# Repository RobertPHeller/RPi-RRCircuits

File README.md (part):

# RPi-RRCircuits

This is a collection of Model Railroad open hardware and open source projects,
using LCC, OpenMRN, and OpenMRN-lite, for the following MCUs and SBCs:

Raspberry Pi, generally as HATs for the "B" flavors (RPi2B, RPi3B and RPi4B).
  (Directories with "HAT" at the end are for these boards.)

Beagle boards, including capes for BeagleBone Black and baseboards for
  PocketBeagles.
  (Directories with "CAPE" at the end are for BeagleBone Blacks,
   directories starting with "BBB" are also boards for the BeagleBone Black,
   directories starting with "PB" or "PocketBeagle" are for the PocketBeagles -
   these boards assume male header pins soldered to the bottom of the 
   PocketBeagle that insert into female header sockets on the base board.)

ESP32 (mostly meant for the Lilygo TTGO-T1 board)
  (Directories starting with "ESP32" are for this board.)

There are a few projects for other boards, including MetroMini (an Adafruit 
mini board that is a Arduino UNO clone), Tiva, and STM's Nucleo board.  The 
directory names will include the name of the board.

Directories ending in OpenMRN contain the Raspberry Pi and Beagle board
software for the various boards.  

These projects were created using Kicad 2013.06.11
(https://launchpad.net/kicad) under CentOS 6 and Kicad 4.0.7 under Ubuntu
18.04. Each subdirectory is one project, and contains a schematic and PCB
design or contains a program for one (or more) projects. There is also
software for the boards using OpenMRN (C++ library for OpenLCB/LCC) for these
projects.

There is a README in each project dir.

## Availble Projects:

1. [16DriverOutputCape](https://github.com/RobertPHeller/RPi-RRCircuits/tree/master/16DriverOutputCape)

    > This is a MCP23017 with two octal buffers meant to drive 16 LEDs (such as 
    > signal lamps). No PWM or special effects.  This board is a Cape for a 
    > BeagleBone Black or Green.  Has address jumpers for the MCP23017 and can be 
    > stacked -- up to 8 of these capes for up to 128 LEDS -- each board has power 
    > terminals for the LEDs.

1. [16DriverOutputHAT](https://github.com/RobertPHeller/RPi-RRCircuits/tree/master/16DriverOutputHAT)

    > This is a MCP23017 with two octal buffers meant to drive 16 LEDs (such as 
    > signal lamps). No PWM or special effects.  This board is a HAT for a 
    > Raspberry Pi 2, 3, or 4.  Has address jumpers for the MCP23017 and can be 
    > stacked -- up to 8 of these hats for up to 128 LEDS -- each board has power 
    > terminals for the LEDs.

1. [16DriverOutputOpenMRN](https://github.com/RobertPHeller/RPi-RRCircuits/tree/master/16DriverOutputOpenMRN)

    > The is the OpenMRN (OpenLCB/LCC) program code for the 16DriverOutput HAT or 
    > Cape boards. Can be build on either a BeagleBoard or a Raspberry Pi for 
    > either. 

1. [16LEDDriver23017SMD](https://github.com/RobertPHeller/RPi-RRCircuits/tree/master/16LEDDriver23017SMD)

    > This is a SMD variant of 16DriverOutputHAT.

1. [16PWMLedDriverCape](https://github.com/RobertPHeller/RPi-RRCircuits/tree/master/16PWMLedDriverCape)

    > This is a PCA9685 with two octal buffers meant to drive 16 LEDs (such as 
    > signal lamps).  This board is much like 16DriverOutputHat, but uses a PWM chip 
    > to allow for special effects and allows for brightness adjustment.  Has 
    > address jumpers for the PCA9685 and can be stacked -- up to 64 boards (WOW) 
    > for up to 1024 LEDs (WOW) -- each board has power terminals for the LEDs.

1. [16PWMLedDriverHat](https://github.com/RobertPHeller/RPi-RRCircuits/tree/master/16PWMLedDriverHat)

    > This is a PCA9685 with two octal buffers meant to drive 16 LEDs (such as 
    > signal lamps).  This board is much like 16DriverOutputHat, but uses a PWM chip 
    > to allow for special effects and allows for brightness adjustment.  Has 
    > address jumpers for the PCA9685 and can be stacked -- up to 64 boards (WOW) 
    > for up to 1024 LEDs (WOW) -- each board has power terminals for the LEDs.

1. [16PWMLedDriverOpenMRN](https://github.com/RobertPHeller/RPi-RRCircuits/tree/master/16PWMLedDriverOpenMRN)

    > This is the OpenMRN (OpenLCB/LCC) program for the 16PWMLedDriver* boards (RPi
    > Hat, BBB Cape, and PocketBeagle board). Can be build on either a BeagleBoard 
    > or a Raspberry Pi for either.

1. [16PWMLedDriverPocketBeagle](https://github.com/RobertPHeller/RPi-RRCircuits/tree/master/16PWMLedDriverPocketBeagle)

    > This is a PCA9685 with two octal buffers meant to drive 16 LEDs (such as
    > signal lamps). This board is much like 16DriverOutputCape, but uses a PWM chip
    > to allow for special effects and allows for brightness adjustment. Has address
    > jumpers for the PCA9685, includes a CAN transceiver with LCC network
    > connectors (RJ45s), 5V power supply for the PocketBeagle, and uses LCC power
    > for the LEDS. It uses female headers for the PocketBeagle (presumes male pin
    > headers soldered to the underside of the PocketBeagle).

1. [BBBCommandStation](https://github.com/RobertPHeller/RPi-RRCircuits/tree/master/BBBCommandStation)

    > Early BeagleBone Black LCC/DCC Command Station board set -- two boards, a cape 
    > and a power board.  Does not include RailComm support.

1. [BBBCommandStationOpenMRN](https://github.com/RobertPHeller/RPi-RRCircuits/tree/master/BBBCommandStationOpenMRN)

    > This is the program for the Beagle Board LCC/DCC/Railcom command 
    > station.  It uses OpenMRN to interface with tha LCC/OpenLCB network
    > to implement a LCC/OpenLCB aware command station node that can 
    > operate DCC/Railcom locomotives.  It should work with any of the
    > Beagle Board addon boards I have designed.  It uses the AM335X's
    > PRUs to generate the DCC signals.  It ises the OpenMRN Console
    > class to communicate over a Tcp/Ip channel with a Tcl/Tk coded
    > GUI program to provide a user friendly point-and-click high level
    > user interface.  

1. [BBBHalfSiding](https://github.com/RobertPHeller/RPi-RRCircuits/tree/master/BBBHalfSiding)

    > Early HalfSiding cape for the Beagle Bone Black. A somewhat all-in-one board
    > for the Beagle Bone Black to manage one half of a siding. This something of a
    > "kitchen sink" board and proably awkard in practice. Probably better off
    > stacking several separate special purpose capes.  I mostly did this as a 
    > "thought experiment" to see what this would look like.  Oh, if it used SMD 
    > parts it might be more compact and might be practical as a single board.

1. [ButtonHat](https://github.com/RobertPHeller/RPi-RRCircuits/tree/master/ButtonHat)

    > This is a RPi HAT board to interface up to 12 push buttons with hardware 
    > debouncing (using 74ahc14 Hex Schmitt-Trigger Inverters) to a RPi.  Jumpers 
    > are used to map the buttons to GPIO pins.  This was a simple "thought 
    > experiment" to see if this was possible.

1. [CANHat](https://github.com/RobertPHeller/RPi-RRCircuits/tree/master/CANHat)

    > This is the original CAN Hat, using the MCP2515 CAN IF Chip and a MCP2551 
    > transceiver chip.

1. [CANHat2](https://github.com/RobertPHeller/RPi-RRCircuits/tree/master/CANHat2)

    > This is the second incarnation of the CAN Hat, also using the MCP2515 and 
    > MCP2551 chips.

1. [CANHat3](https://github.com/RobertPHeller/RPi-RRCircuits/tree/master/CANHat3)

    > This is the third incarnation of the CAN Hat, also using the MCP2515 and 
    > MCP2551 chips.

1. [DCCOD_SMD](https://github.com/RobertPHeller/RPi-RRCircuits/tree/master/DCCOD_SMD)

    > Single current sensing occupancy detector, meant for ESP32-16xDCCOD or 
    > simular.  Meant as a thought experiment to see what this would cost, etc.

1. [DCCShield](https://github.com/RobertPHeller/RPi-RRCircuits/tree/master/DCCShield)

    > Simple DCC driver shield for Arduino.

1. [DCCTiva](https://github.com/RobertPHeller/RPi-RRCircuits/tree/master/DCCTiva)

    > Simple DCC Driver board for Tiva.

1. [DualUncouplerHAT](https://github.com/RobertPHeller/RPi-RRCircuits/tree/master/DualUncouplerHAT)

    > This a dual driver for a electromagnetic uncoupler coil.  It features a 
    > pair of 555 type timers (in the form of a 556 dual timer) driving a TIP120 
    > power darlington.  It uses GPIO pins 21 and 22 (BCM 5 and 6, physical pins 
    > 29 and 31).

1. [DualUncouplerHAT1](https://github.com/RobertPHeller/RPi-RRCircuits/tree/master/DualUncouplerHAT1)

    > This is the same as DualUncouplerHAT, except it uses GPIO pins 23 and 24 
    > (BCM 13 and 19, physical pins 33 and 35).

1. [ESP32-16LedDriver](https://github.com/RobertPHeller/RPi-RRCircuits/tree/master/ESP32-16LedDriver)

    > 16 on/off LED Driver board using a MCP23017.

1. [ESP32-16PWMLedDriver](https://github.com/RobertPHeller/RPi-RRCircuits/tree/master/ESP32-16PWMLedDriver)

    > 16 LED PWM driver board using a PCA9685.

1. [ESP32-16xDCCOD](https://github.com/RobertPHeller/RPi-RRCircuits/tree/master/ESP32-16xDCCOD)

    > Backplane for up to 16 DCCOD_SMD's using a ESP32 MCU.  Meant as a thought 
    > experiment to see what this would cost, etc.

1. [ESP32-C3-Booster](https://github.com/RobertPHeller/RPi-RRCircuits/tree/master/ESP32-C3-Booster)

    > ESP32 C3 based DCC Booster.

1. [ESP32-C3-BoosterOpenMRNIDF](https://github.com/RobertPHeller/RPi-RRCircuits/tree/master/ESP32-C3-BoosterOpenMRNIDF)

    > 

1. [ESP32-D0WD-V3-MultiFunctionOpenMRNIDF](https://github.com/RobertPHeller/RPi-RRCircuits/tree/master/ESP32-D0WD-V3-MultiFunctionOpenMRNIDF)

    > 

1. [ESP32-HalfSiding](https://github.com/RobertPHeller/RPi-RRCircuits/tree/master/ESP32-HalfSiding)

    > First draft of a ESP32 HalfSiding node using a MCP23017 on/off signal lamps.

1. [ESP32-MultiFunction](https://github.com/RobertPHeller/RPi-RRCircuits/tree/master/ESP32-MultiFunction)

    > This is a circuit board that supports an ESP32 Dev Kit board or TTGO-T1 board
    > to manage a range of possible interlocking plants or other model railroad
    > situations. It contains four stall motor drivers with point sense, four CT
    > Coil type occupancy detectors, four Schmitt-Trigger inputs (for push buttons),
    > four driver outputs, and 16 PWM LED drivers.

1. [ESP32-PWMHalfSiding](https://github.com/RobertPHeller/RPi-RRCircuits/tree/master/ESP32-PWMHalfSiding)

    > This is a circuit board that supports an ESP32 Dev Kit board or TTGO-T1 board 
    > to manage one half (one end) of a siding.  This board can also be used to 
    > manage two bi-directional single track ABS blocks or one bi-directional dual 
    > track ABS block.  There are other trackwork cases this board can handle as 
    > well.  

1. [ESP32-PWMHalfSidingSMD-T7](https://github.com/RobertPHeller/RPi-RRCircuits/tree/master/ESP32-PWMHalfSidingSMD-T7)

    > This is a circuit board that supports an ESP32 Dev Kit board or TTGO-T1 board 
    > to manage one half (one end) of a siding.  This board can also be used to 
    > manage two bi-directional single track ABS blocks or one bi-directional dual 
    > track ABS block.  There are other trackwork cases this board can handle as 
    > well.  

1. [ESP32-PWMHalfSidingSMD](https://github.com/RobertPHeller/RPi-RRCircuits/tree/master/ESP32-PWMHalfSidingSMD)

    > This is a circuit board that supports an ESP32 Dev Kit board or TTGO-T1 board 
    > to manage one half (one end) of a siding.  This board can also be used to 
    > manage two bi-directional single track ABS blocks or one bi-directional dual 
    > track ABS block.  There are other trackwork cases this board can handle as 
    > well.  

1. [ESP32-S3-MultiFunction](https://github.com/RobertPHeller/RPi-RRCircuits/tree/master/ESP32-S3-MultiFunction)

    > This is a LCC node circuit board that is based around an Espressif ESP32-S3FN8
    > MCU to manage and operate a collection of model railroad sensors and
    > actuators. 

1. [ESP32-S3-MultiFunctionOpenMRNIDF](https://github.com/RobertPHeller/RPi-RRCircuits/tree/master/ESP32-S3-MultiFunctionOpenMRNIDF)

    > 

1. [ESP32_mini_KiCad_Library](https://github.com/RobertPHeller/RPi-RRCircuits/tree/master/ESP32_mini_KiCad_Library)

    > KiCad symbol and footprint for the ESP32 Mini, the ESP32 clone of the Wemos D1 mini with more pins and more power!
    > There is some info on the boards [here](https://www.reddit.com/r/esp8266/comments/a93raj/wemos_ttgo_mini_d1_esp32/). It seems to be a Wemos clone, but is def. not made by them. I really like the boards for the small size and cheap price while giving me the power of an ESP32 and much more IO compared to the Wemos D1 mini.

1. [ESP32ABSBoard](https://github.com/RobertPHeller/RPi-RRCircuits/tree/master/ESP32ABSBoard)

    > ESP32 ABS (Automatic Block Signal) board.  Very simple board: one block 
    > detector, 8 LED drivers.

1. [ESP32BaseBoard](https://github.com/RobertPHeller/RPi-RRCircuits/tree/master/ESP32BaseBoard)

    > ESP32 Base board.  Base starting point for a ESP32 node.

1. [ESP32MRNSketches](https://github.com/RobertPHeller/RPi-RRCircuits/tree/master/ESP32MRNSketches)

    > ESP32 Arduino / OpenMRNLite sketches for the ESP32 boards.

1. [ESP32QuadOCDect](https://github.com/RobertPHeller/RPi-RRCircuits/tree/master/ESP32QuadOCDect)

    > ESP32 Quad Occupancy Detector node.

1. [ESP32QuadSMCSense](https://github.com/RobertPHeller/RPi-RRCircuits/tree/master/ESP32QuadSMCSense)

    > ESP32 Quad Stall Motor w/ sense node.

1. [LCCCANCape](https://github.com/RobertPHeller/RPi-RRCircuits/tree/master/LCCCANCape)

    > LCC/CAN Transceiver Cape for the Beagle Bone.

1. [LEDDriverHat](https://github.com/RobertPHeller/RPi-RRCircuits/tree/master/LEDDriverHat)

    > Eight LED drivers.  Jumpers to select GPIO pins.

1. [MCP23017Hat](https://github.com/RobertPHeller/RPi-RRCircuits/tree/master/MCP23017Hat)

    > This is a 16 pin I2C port expander using a MCP230017.

1. [OpenMRNIDF](https://github.com/RobertPHeller/RPi-RRCircuits/tree/master/OpenMRNIDF)

    > This is an exported version of the OpenMRN library for the ESP32 which is
    > usable as an ESP-IDF component.

1. [PBCommandStation](https://github.com/RobertPHeller/RPi-RRCircuits/tree/master/PBCommandStation)

    > Original through hole version of the Pocket Beagle LCC/DCC Command Station.
    > This design is depreciated -- see PocketBeagleCommandStation and 
    > PocketBeagleCommandStation_SMD for a current design.

1. [PocketBeagleCommandStation](https://github.com/RobertPHeller/RPi-RRCircuits/tree/master/PocketBeagleCommandStation)

    > Through hole version of the PocketBeagle LCC/DCC Command Station. This is a
    > DCC command station that is a LCC node. It implements the OpenLCB train
    > protocol node over LCC and converts that to DCC commands. It includes a
    > booster and puts the DCC signal on the LCC bus (pins 4 and 5). It implements a
    > programming track and implements Railcom. The Command Station uses a
    > PocketBeagle as the processing element and uses the PRUs (Programmable
    > Realtime Units) to generate the DCC signal. (See
    > [PocketBeagleCommandStation_SMD](https://github.com/RobertPHeller/RPi-RRCircuits/tree/master/PocketBeagleCommandStation_SMD)
    > for a SMD version.)

1. [PocketBeagleCommandStation_SMD](https://github.com/RobertPHeller/RPi-RRCircuits/tree/master/PocketBeagleCommandStation_SMD)

    > SMD version of the PocketBeagle LCC/DCC Command Station.  This is a
    > DCC command station that is a LCC node. It implements the OpenLCB train
    > protocol node over LCC and converts that to DCC commands. It includes a
    > booster and puts the DCC signal on the LCC bus (pins 4 and 5). It implements a
    > programming track and implements Railcom. The Command Station uses a
    > PocketBeagle as the processing element and uses the PRUs (Programmable
    > Realtime Units) to generate the DCC signal. (See
    > [PocketBeagleCommandStation](https://github.com/RobertPHeller/RPi-RRCircuits/tree/master/PocketBeagleCommandStation)
    > for a through hole version.)

1. [PocketBeagleMultifuntion](https://github.com/RobertPHeller/RPi-RRCircuits/tree/master/PocketBeagleMultifuntion)

    > This is a circuit board that supports a PocketBeagle board to manage a range
    > of possible interlocking plants or other model railroad situations. It
    > contains four stall motor drivers with point sense, four CT Coil type
    > occupancy detectors, four Schmitt-Trigger inputs (for push buttons), four
    > driver outputs, 8 GPIO pins in a 5x2 header, and 16 PWM LED drivers. 

1. [PocketBeagleMultifuntionOpenMRN](https://github.com/RobertPHeller/RPi-RRCircuits/tree/master/PocketBeagleMultifuntionOpenMRN)

    > OpenMRN program for the PocketBeagleMultifuntion board.

1. [PocketBeagleQuadOCDect](https://github.com/RobertPHeller/RPi-RRCircuits/tree/master/PocketBeagleQuadOCDect)

    > PocketBeagle Quad Occupancy Detector.

1. [PocketBeagleQuadSMCSense](https://github.com/RobertPHeller/RPi-RRCircuits/tree/master/PocketBeagleQuadSMCSense)

    > PocketBeagle Quad Stall Motor w/ Sense.

1. [QuadOCDectCape](https://github.com/RobertPHeller/RPi-RRCircuits/tree/master/QuadOCDectCape)

    > Quad Occupancy detector Cape (for a Beagle Bone).

1. [QuadOCDectHat](https://github.com/RobertPHeller/RPi-RRCircuits/tree/master/QuadOCDectHat)

    > Quad Occupancy detector Hat for Raspberry Pi.

1. [QuadOCDectOpenMRN](https://github.com/RobertPHeller/RPi-RRCircuits/tree/master/QuadOCDectOpenMRN)

    > OpenMRN (LCC / OpenLCB) program for Quad Occupancy Detector boards for Linux
    > SBCs.

1. [QuadSMC](https://github.com/RobertPHeller/RPi-RRCircuits/tree/master/QuadSMC)

    > This is a generic quad verison of SMCSenseHAT.

1. [QuadSMCSenseCape](https://github.com/RobertPHeller/RPi-RRCircuits/tree/master/QuadSMCSenseCape)

    > Quad Stall Motor w/ Sense Cape for a Beagle Bone.

1. [QuadSMCSenseHat](https://github.com/RobertPHeller/RPi-RRCircuits/tree/master/QuadSMCSenseHat)

    > Quad Stall Motor w/ Sense Hat for a Raspberry Pi.

1. [QuadSMCSenseOpenMRN](https://github.com/RobertPHeller/RPi-RRCircuits/tree/master/QuadSMCSenseOpenMRN)

    > OpenMRN (LCC / OpenLCB) program for Linux SBC with QuadSMCSense addon boards.

1. [QuadUncoupler](https://github.com/RobertPHeller/RPi-RRCircuits/tree/master/QuadUncoupler)

    > This is a generic qad version of DualUncouplerHAT.

1. [SignalHAT](https://github.com/RobertPHeller/RPi-RRCircuits/tree/master/SignalHAT)

    > This is a hat containing a MAX7221 driven off level shifted SPI.  It can 
    > drive up to 8 common-cathode signals of up to 8 LEDs each.

1. [SMCSenseHAT](https://github.com/RobertPHeller/RPi-RRCircuits/tree/master/SMCSenseHAT)

    > This is a dual stall motor driver and point sense circuit.  The stall 
    > motor driver uses a MPQ3725A transistor to allow driving either multiple 
    > Tortoises in parallel (eg for a crossover) or newer Switchmaster or 
    > Torquemaster which draw more current than the LM324 can handle.  Also 
    > included is a point sense circuit built from a RS Flip Flop made from 
    > 2-input NAND gates.  The point sense circuit expects to be connected to a 
    > single pole double throw switch, either a built in one in the Tortoise or 
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
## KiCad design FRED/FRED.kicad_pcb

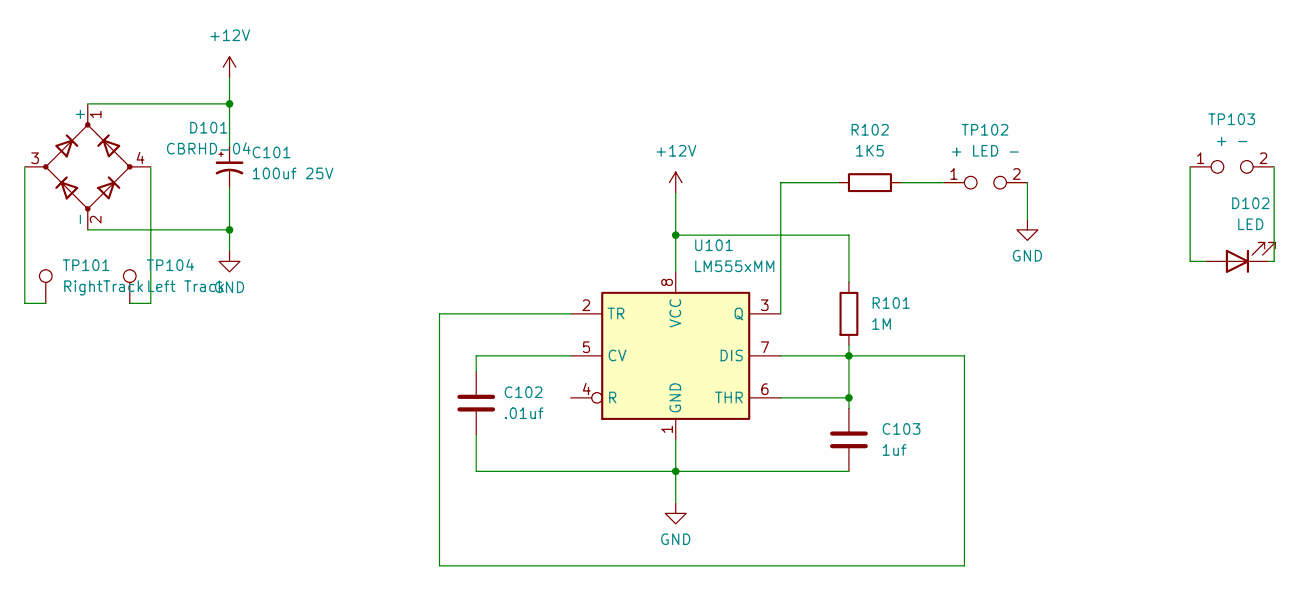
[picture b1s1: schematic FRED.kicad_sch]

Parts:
C101: 100uf 25V; CP_EIA-7361-438_AVX-U; Mouser Part Number 581-TRJU107K025RRJV
C102: .01uf; C_0402_1005Metric; Mouser Part Number 603-CC402JRX7R8BB103
C103: 1uf; C_0402_1005Metric; Mouser Part Number 603-CC402KRX5R6BB105
D101: CBRHD-04; SOP250P700X290-4N; Mouser Part Number 610-CBRHD04-PB
D102: LED; LED_0201_0603Metric; Mouser Part Number 743-IN-S21AT5R
R101: 1M; R_0402_1005Metric; Mouser Part Number 652-CR0402FX-1003GLF
R102: 1K5; R_0402_1005Metric; Mouser Part Number 652-CR0402FX-1501GLF
TP101: RightTrack; Track Pickup Pad
TP102: + LED -; SolderWire-0.1sqmm_1x02_P3.6mm_D0.4mm_OD1mm
TP103: + -; SolderPads_1x2_1.2mm
TP104: Left Track; Track Pickup Pad
U101: LM555xMM; VSSOP-8_3.0x3.0mm_P0.65mm; Mouser Part Number 926-LM555CMMX/NOPB

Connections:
+12V: C101.1, D101.1 (+), R101.1, U101.8 (VCC)
GND: C101.2, C102.2, C103.2, D101.2 (-), TP102.2, U101.1 (GND)
unnamed: C102.1, U101.5 (CV)
unnamed: C103.1, R101.2, U101.2 (TR), U101.6 (THR), U101.7 (DIS)
unnamed: D101.3, TP101.1
unnamed: D101.4, TP104.1
unnamed: D102.1 (K), TP103.2
unnamed: D102.2 (A), TP103.1
unnamed: R102.1, U101.3 (Q)
unnamed: R102.2, TP102.1

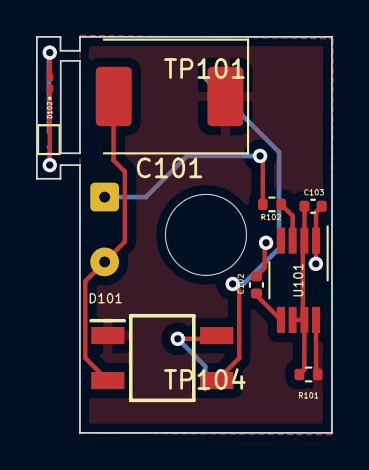
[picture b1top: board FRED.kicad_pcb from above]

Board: 2 copper layers, 16.4 x 22.0 mm, 12 parts (0 on the bottom side), 10 nets.

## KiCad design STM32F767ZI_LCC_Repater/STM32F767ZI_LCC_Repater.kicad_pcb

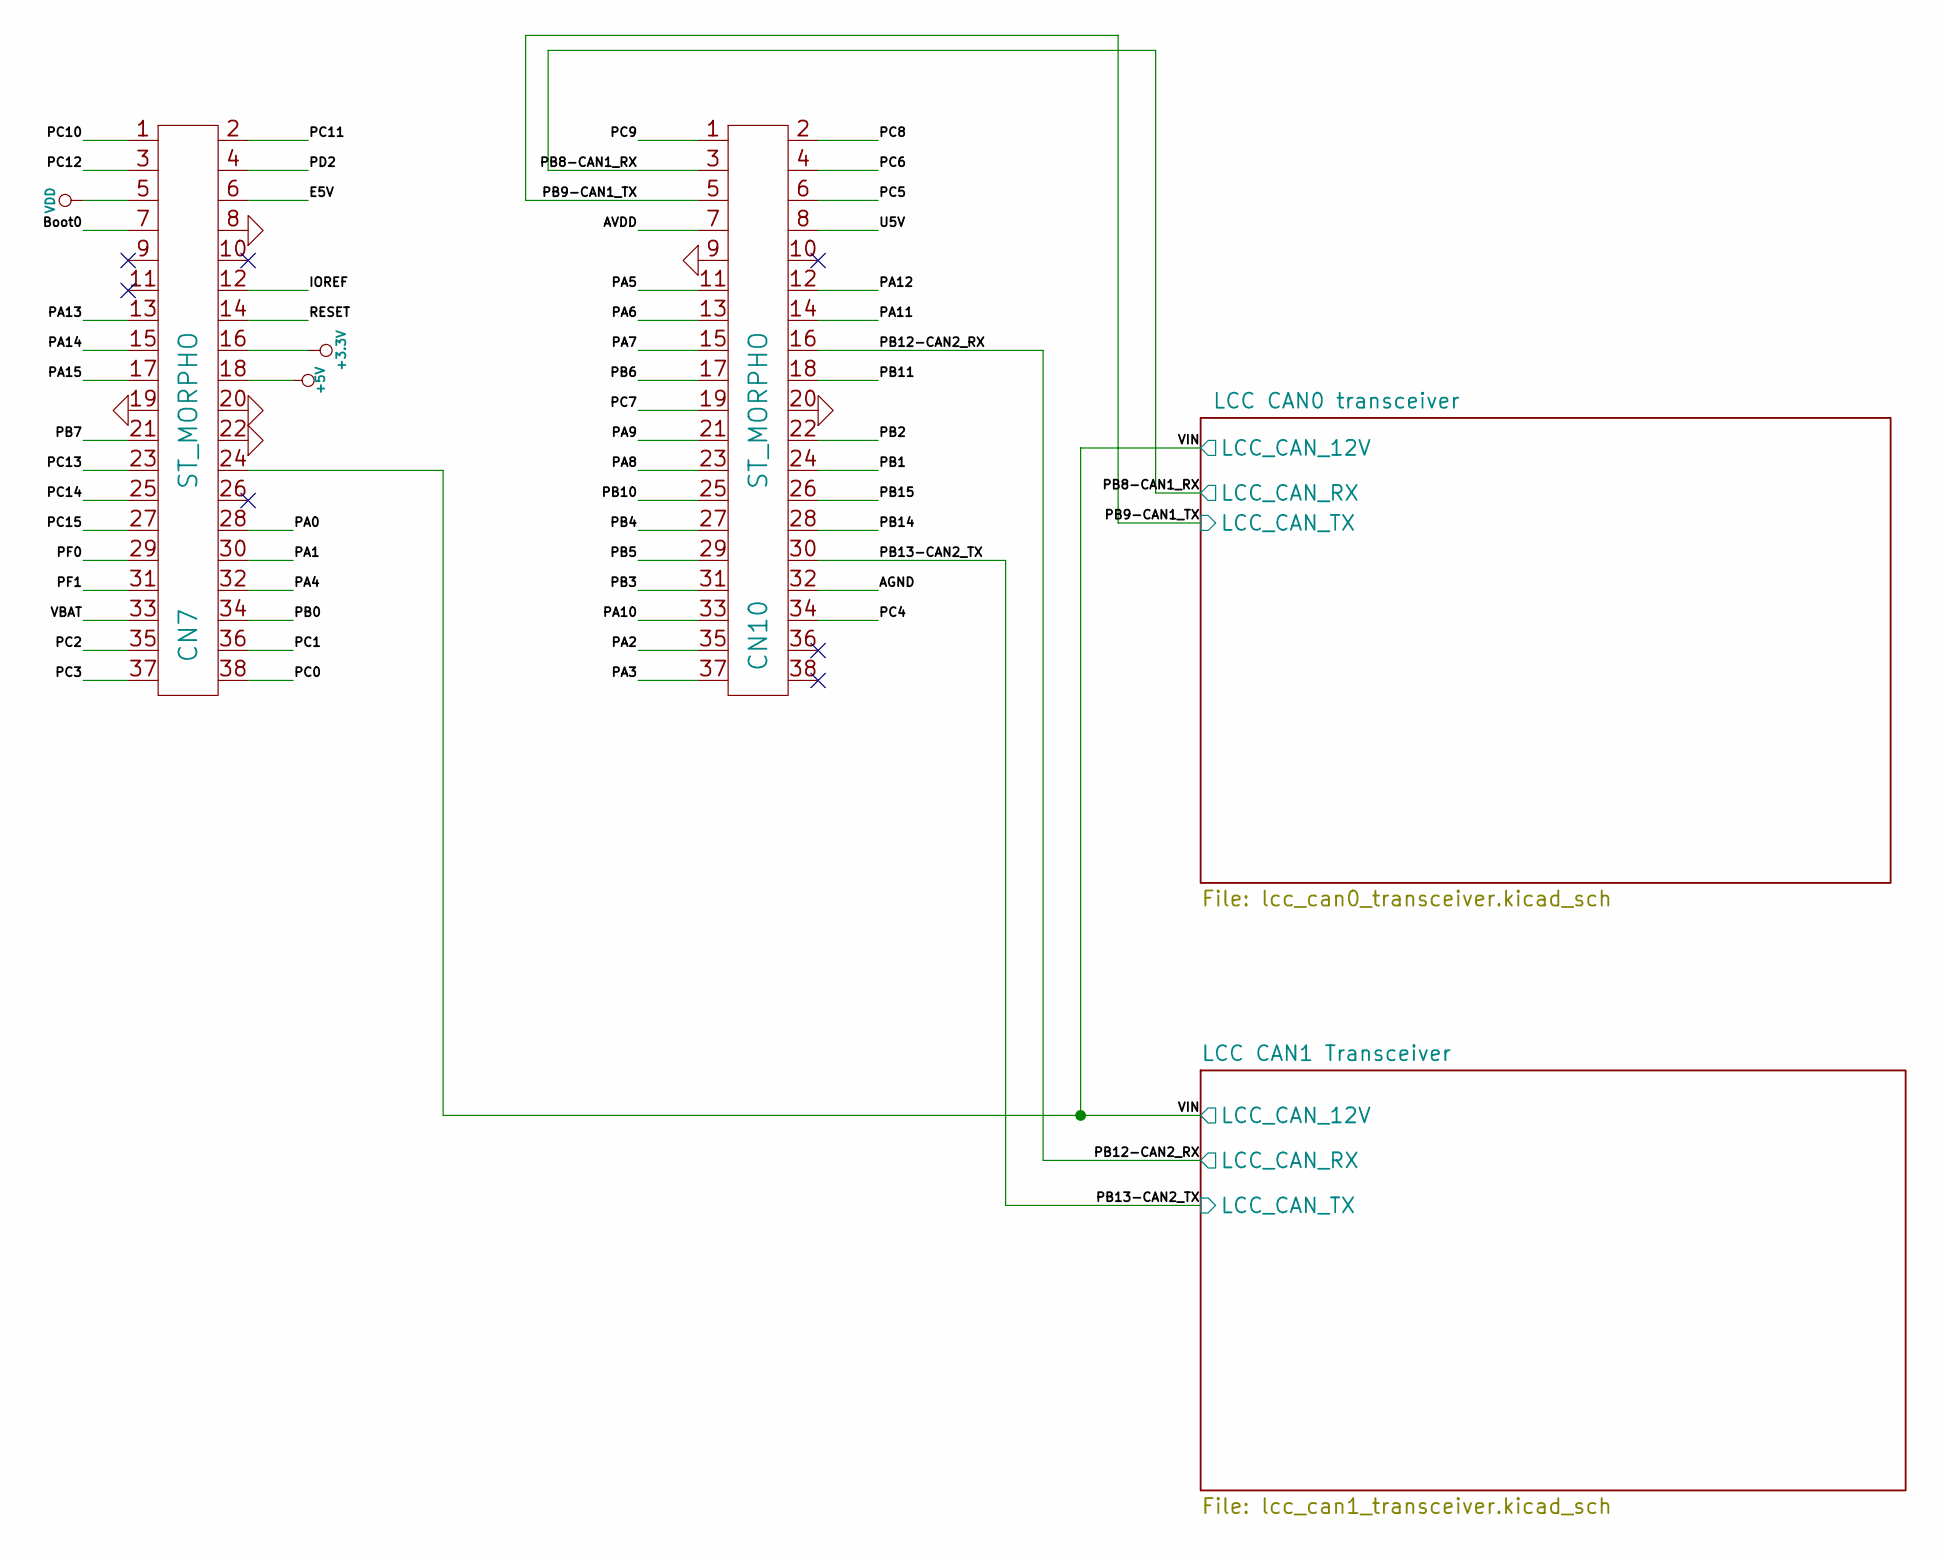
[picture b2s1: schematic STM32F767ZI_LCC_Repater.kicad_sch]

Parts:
CN7, CN10: ST_MORPHO; ST_Morpho

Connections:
+3.3V: CN7.16; also elsewhere on the board
+5V: CN7.18
/AGND: CN10.32
/AVDD: CN10.7
/Boot0: CN7.7
/E5V: CN7.6
/IOREF: CN7.12
/PA0: CN7.28
/PA1: CN7.30
/PA2: CN10.35
/PA3: CN10.37
/PA4: CN7.32
/PA5: CN10.11
/PA6: CN10.13
/PA7: CN10.15
/PA8: CN10.23
/PA9: CN10.21
/PA10: CN10.33
/PA11: CN10.14
/PA12: CN10.12
/PA13: CN7.13
/PA14: CN7.15
/PA15: CN7.17
/PB0: CN7.34
/PB1: CN10.24
/PB2: CN10.22
/PB3: CN10.31
/PB4: CN10.27
/PB5: CN10.29
/PB6: CN10.17
/PB7: CN7.21
/PB8-CAN1_RX: CN10.3; also elsewhere on the board
/PB9-CAN1_TX: CN10.5; also elsewhere on the board
/PB10: CN10.25
/PB11: CN10.18
/PB12-CAN2_RX: CN10.16; also elsewhere on the board
/PB13-CAN2_TX: CN10.30; also elsewhere on the board
/PB14: CN10.28
/PB15: CN10.26
/PC0: CN7.38
/PC1: CN7.36
/PC2: CN7.35
/PC3: CN7.37
/PC4: CN10.34
/PC5: CN10.6
/PC6: CN10.4
/PC7: CN10.19
/PC8: CN10.2
/PC9: CN10.1
/PC10: CN7.1
/PC11: CN7.2
/PC12: CN7.3
/PC13: CN7.23
/PC14: CN7.25
/PC15: CN7.27
/PD2: CN7.4
/PF0: CN7.29
/PF1: CN7.31
/RESET: CN7.14
/U5V: CN10.8
/VBAT: CN7.33
/VIN: CN7.24; also elsewhere on the board
GND: CN7.8, CN7.19, CN7.20, CN7.22, CN10.9, CN10.20; also elsewhere on the board
VDD: CN7.5

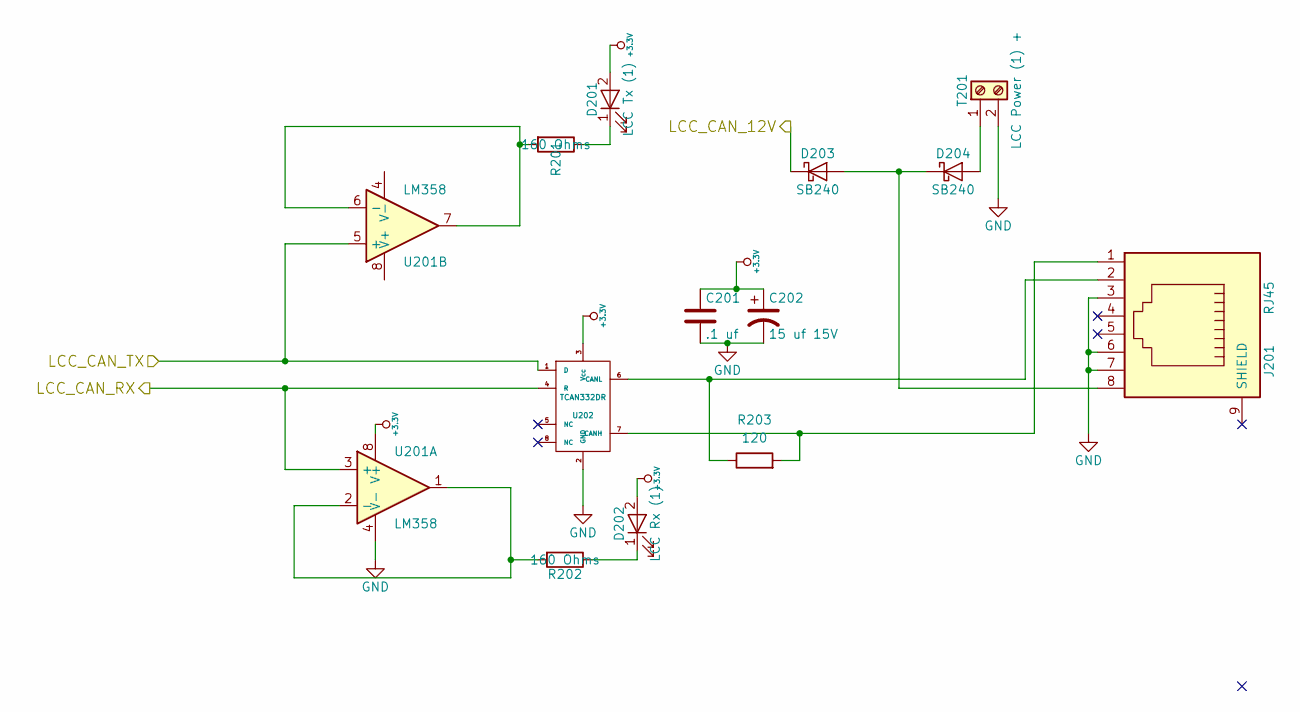
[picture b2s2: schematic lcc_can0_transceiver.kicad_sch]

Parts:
C201: .1 uf; C_0603_1608Metric; Mouser Part Number 603-CC603KPX7R9BB104
C202: 15 uf 15V; CP_Elec_4x5.8; Mouser Part Number 647-UUD1C150MCL
D201: LCC Tx (1); LED_0603_1608Metric; Mouser Part Number 710-150060SS75000
D202: LCC Rx (1); LED_0603_1608Metric; Mouser Part Number 710-150060YS75000
D203, D204: SB240; D_PowerDI-123; Mouser Part Number 621-DFLS240-7
J201: RJ45; RJ45_8N-S; Mouser Part Number 710-615008144221
R201, R202: 160 Ohms; R_0603_1608Metric; Mouser Part Number 603-AC0603JR-07160RL
R203: 120; R_0603_1608Metric; Mouser Part Number 603-RT0603DRE07120RL
T201: LCC Power (1) +; TerminalBlock_TE_282834-2_1x02_P2.54mm_Horizontal; Mouser Part Number 651-1725656
U201: LM358; SOIC-8_3.9x4.9mm_P1.27mm; Mouser Part Number 595-LM358DR
U202: TCAN332DR; SOIC-8_3.9x4.9mm_P1.27mm; Mouser Part Number 595-TCAN332DR

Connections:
+3.3V: C201.1, C202.1, D201.2 (A), D202.2 (A), U201.8 (V+), U202.3 (Vcc); also elsewhere on the board
/PB8-CAN1_RX: U201.3 (+), U202.4 (R); also elsewhere on the board
/PB9-CAN1_TX: U201.5 (+), U202.1 (D); also elsewhere on the board
/VIN: D203.1 (K); also elsewhere on the board
GND: C201.2, C202.2, J201.3, J201.6, J201.7, T201.2, U201.4 (V-), U202.2 (GND); also elsewhere on the board
unnamed: D201.1 (K), R201.1
unnamed: D202.1 (K), R202.1
unnamed: D203.2 (A), D204.1 (K), J201.8
unnamed: D204.2 (A), T201.1
unnamed: J201.1, R203.2, U202.7 (CANH)
unnamed: J201.2, R203.1, U202.6 (CANL)
unnamed: R201.2, U201.6 (-), U201.7
unnamed: R202.2, U201.1, U201.2 (-)

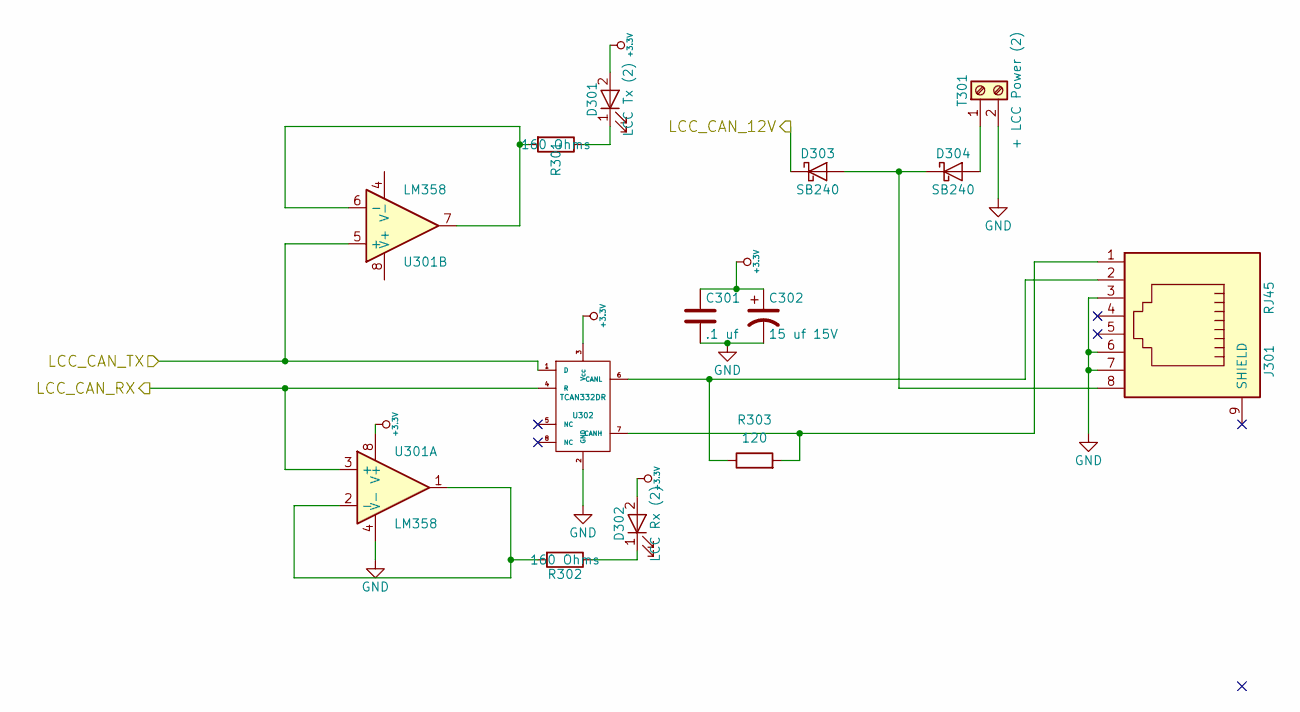
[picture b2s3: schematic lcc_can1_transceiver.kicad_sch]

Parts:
C301: .1 uf; C_0603_1608Metric; Mouser Part Number 603-CC603KPX7R9BB104
C302: 15 uf 15V; CP_Elec_4x5.8; Mouser Part Number 647-UUD1C150MCL
D301: LCC Tx (2); LED_0603_1608Metric; Mouser Part Number 710-150060SS75000
D302: LCC Rx (2); LED_0603_1608Metric; Mouser Part Number 710-150060YS75000
D303, D304: SB240; D_PowerDI-123; Mouser Part Number 621-DFLS240-7
J301: RJ45; RJ45_8N-S; Mouser Part Number 710-615008144221
R301, R302: 160 Ohms; R_0603_1608Metric; Mouser Part Number 603-AC0603JR-07160RL
R303: 120; R_0603_1608Metric; Mouser Part Number 603-RT0603DRE07120RL
T301: + LCC Power (2); TerminalBlock_TE_282834-2_1x02_P2.54mm_Horizontal; Mouser Part Number 651-1725656
U301: LM358; SOIC-8_3.9x4.9mm_P1.27mm; Mouser Part Number 595-LM358DR
U302: TCAN332DR; SOIC-8_3.9x4.9mm_P1.27mm; Mouser Part Number 595-TCAN332DR

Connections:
+3.3V: C301.1, C302.1, D301.2 (A), D302.2 (A), U301.8 (V+), U302.3 (Vcc); also elsewhere on the board
/PB12-CAN2_RX: U301.3 (+), U302.4 (R); also elsewhere on the board
/PB13-CAN2_TX: U301.5 (+), U302.1 (D); also elsewhere on the board
/VIN: D303.1 (K); also elsewhere on the board
GND: C301.2, C302.2, J301.3, J301.6, J301.7, T301.2, U301.4 (V-), U302.2 (GND); also elsewhere on the board
unnamed: D301.1 (K), R301.1
unnamed: D302.1 (K), R302.1
unnamed: D303.2 (A), D304.1 (K), J301.8
unnamed: D304.2 (A), T301.1
unnamed: J301.1, R303.2, U302.7 (CANH)
unnamed: J301.2, R303.1, U302.6 (CANL)
unnamed: R301.2, U301.6 (-), U301.7
unnamed: R302.2, U301.1, U301.2 (-)

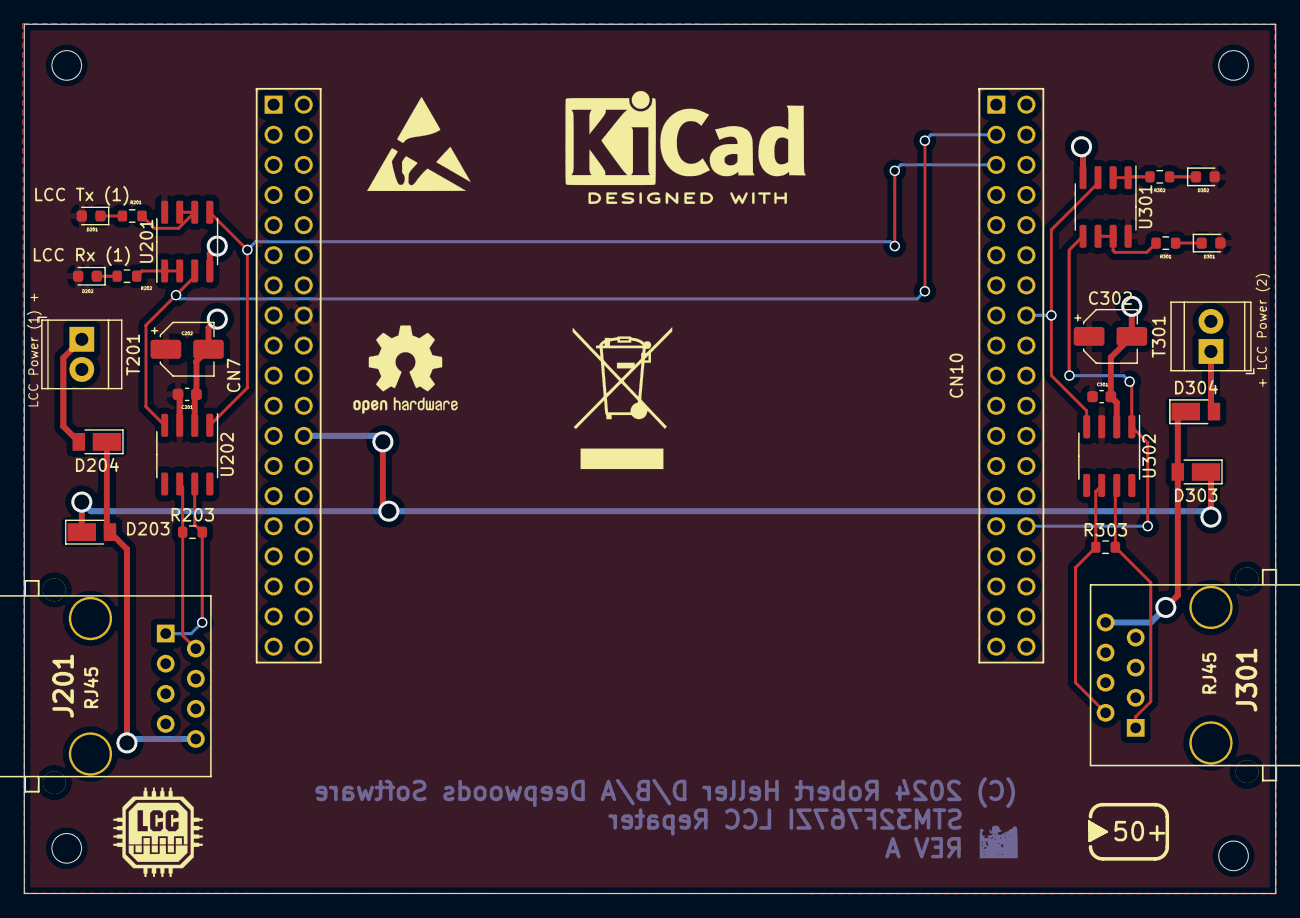
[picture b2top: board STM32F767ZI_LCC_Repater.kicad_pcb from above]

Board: 2 copper layers, 105.6 x 73.3 mm, 32 parts (0 on the bottom side), 23 nets.

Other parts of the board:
MH: MountingHole_2-5mm_RevA_Date21Jun2010
MH#2, MH#3, MH#4: MountingHole_2-5mm_RevA_Date21Jun2010

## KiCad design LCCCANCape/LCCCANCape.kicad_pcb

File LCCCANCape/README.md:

# LCCCANCape

LCC/CAN Transceiver Cape for the Beagle Bone.

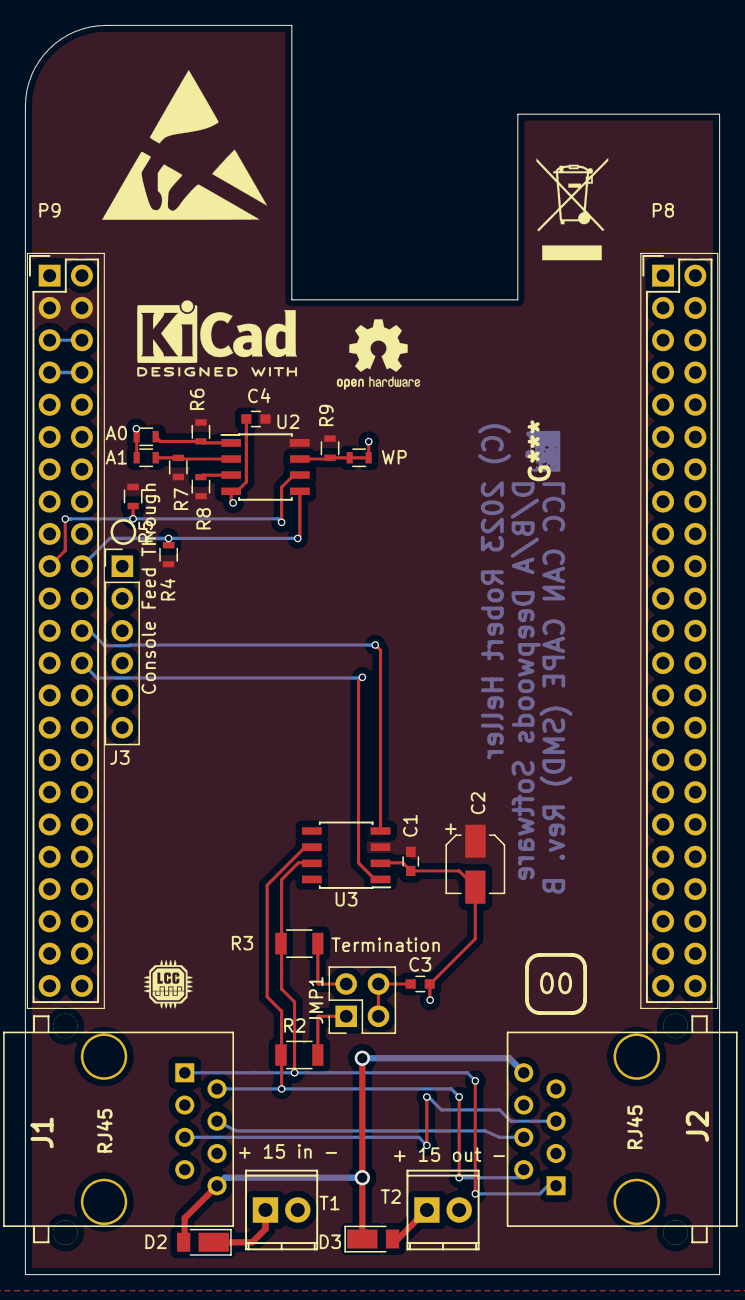
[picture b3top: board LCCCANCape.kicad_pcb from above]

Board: 2 copper layers, 54.6 x 98.3 mm, 27 parts (0 on the bottom side), 22 nets.

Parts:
C1, C4: .1 uf; C_0603
C2: 15 uf 35V; CP_Elec_4x5.7
C3: 47 nf; C_0603
D2, D3: DFLS240-7; D_PowerDI-123
J1, J2: RJ45; RJ45_8N-S
J3: Console Feed Through; Pin_Header_Straight_1x06_Pitch2.54mm
JMP1: Termination; Pin_Header_Straight_2x02_Pitch2.54mm
JP1: A0; JP_0603_Open
JP2: A1; JP_0603_Open
JP3: WP; JP_0603_Closed
P8, P9: BeagleBone_Black_Header; Socket_BeagleBone_Black
R2, R3: 60 Ohms; R_1206
R4, R5: 5.6K; R_0603
R6, R7, R8: 4.75K; R_0603
R9: 10K; R_0603
T1: + 15 in -; TerminalBlock_Phoenix_MPT-2.54mm_2pol
T2: + 15 out -; TerminalBlock_Phoenix_MPT-2.54mm_2pol
U2: CAT24C256W; SOIC-8_3.9x4.9mm_Pitch1.27mm
U3: TCAN332DR; SOIC-8_3.9x4.9mm_Pitch1.27mm

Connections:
+3V3: C1.1, C2.1, C4.1, P9.3, P9.4, R4.1, R5.1, R6.1, R7.1, R8.1, R9.1, U2.8, U3.3
+5V: P9.5, P9.6
/CANH: J1.1, J2.1, R3.1, U3.7
/CANL: J1.2, J2.2, R2.1, U3.6
/CANRX: P9.24, U3.4
/CANTX: P9.26, U3.1
/SCL: P9.19, R5.2, U2.6
/SDA: P9.20, R4.2, U2.5
GND: C1.2, C2.2, C3.2, C4.2, J1.3, J1.6, J1.7, J2.3, J2.6, J2.7, JP1.1, JP2.1, JP3.1, P8.1, P8.2, P9.1, P9.2, P9.43, P9.44, P9.45, P9.46, T1.2, T2.2, U2.4, U3.2
unnamed: C3.1, JMP1.3, JMP1.4
unnamed: D2.1, T1.1
unnamed: D2.2, D3.1, J1.8, J2.8
unnamed: D3.2, T2.1
unnamed: J1.4, J2.4
unnamed: J1.5, J2.5
unnamed: JMP1.1, R2.2
unnamed: JMP1.2, R3.2
unnamed: JP1.2, R6.2, U2.1
unnamed: JP2.2, R7.2, U2.2
unnamed: JP3.2, R9.2, U2.7
unnamed: R8.2, U2.3
SYS_5V: P9.7, P9.8

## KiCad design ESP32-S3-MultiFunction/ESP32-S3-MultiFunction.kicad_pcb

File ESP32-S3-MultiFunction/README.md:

# ESP32-S3-MultiFunction

This is a LCC node circuit board that is based around an Espressif ESP32-S3FN8
MCU to manage and operate a collection of model railroad sensors and
actuators. 

The board contains these I/O sections:

- Four occupancy detectors. CT Coil type sensors, so they won't work with DC
systems without an AC bias.
- Four stall-motor drivers with point sense.
- Four Schmitt Trigger inputs, meant for push buttons.
- Four Buffered outputs, by default for Panel LEDS, but with drop in
resistors, can also drive relays or other loads.
- Sixteen PWM Led drivers. These are meant to light (LED) lamps in signal
heads.

The board connects to a LCC network and utilizes the Event Transport Protocol
in its operation. It also uses a CDI to describe its configuration. It can be
configured with JMRI or other available LCC configuration tools.

The board draws about 30ma, plus load. Circuitron specifies that a Tortoise
switch machine draws about 16ma when stalled, so four Tortoise switch machines
would add 64ma. There is a terminal block near the stall motor terminal blocks
to optionally provide external power for the switch machines. There are 16
signal lamp outputs that have 1.5K Ohm load resistors, this means about 8ma
per LED. If all lamps are on at full brightness, this comes to 128ma, although
turning all 16 signal on full at a time is not likely to be prototypical,
since most signal aspects only light one lamp per head. There is a terminal
block to optionally supply external power for the signal lamps, as a way to
reduce the load on the LCC power bus. The buffered output section uses an
external power source, so does not add any load to the LCC power bus.

This board is a multi-purpose board that can be used in a number of
situations, including (but not limited to): one end of a siding, a yard or
terminal throat, ABS, and interlocking plants.</p>

The first five of these boards are being fabricated by
[PCBWay](https://www.pcbway.com/orderonline.aspx), which I have used for my
other boards. They do an excellent job and I recommend them to anyone seeking
to get a small run of PCBs made, either bare boards or fully assembled boards.

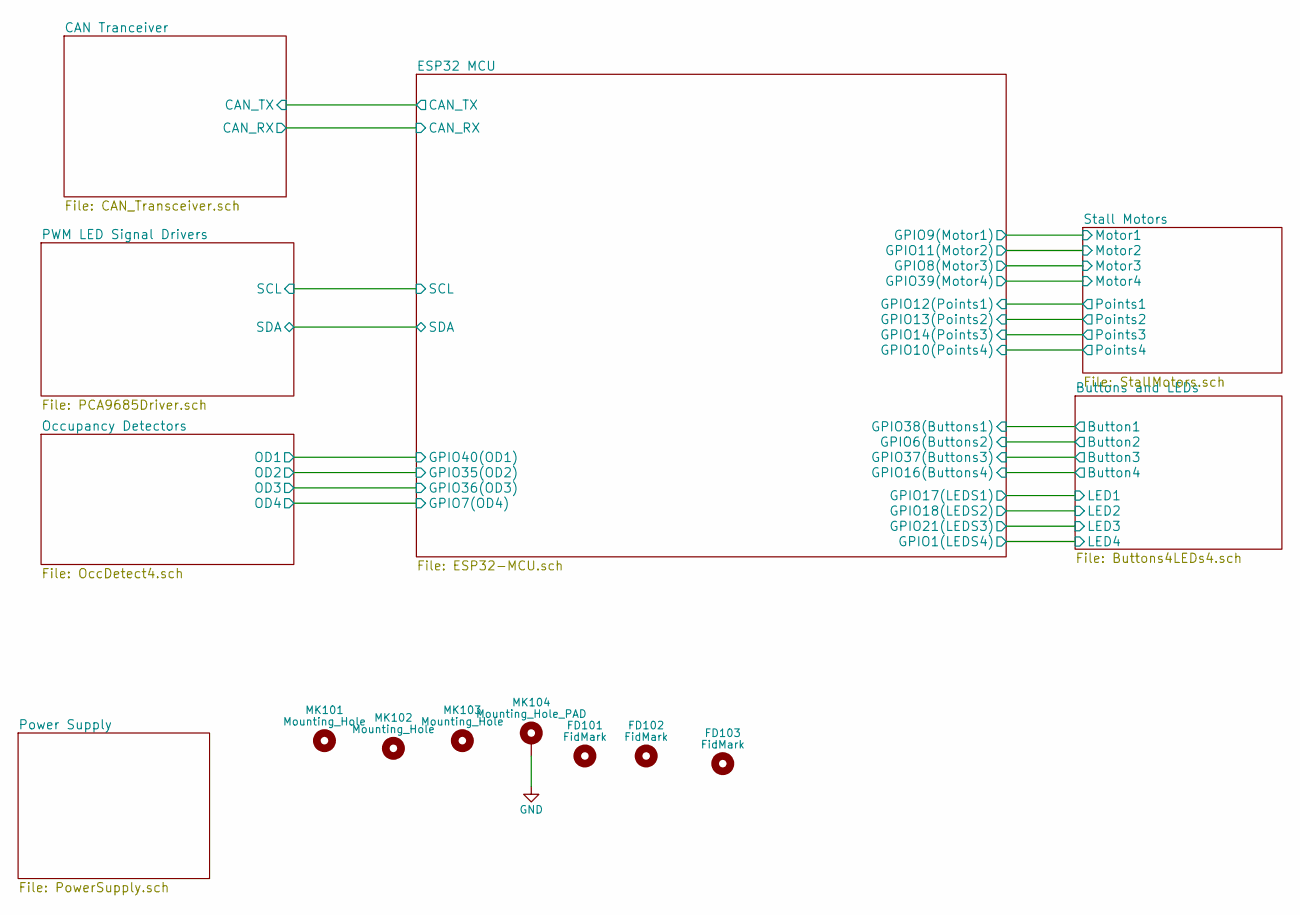
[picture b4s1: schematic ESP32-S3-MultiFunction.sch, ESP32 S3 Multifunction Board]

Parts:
FD101, FD102, FD103: FidMark; Fiducial_1mm_Dia_2.54mm_Outer_CopperTop
MK101, MK102, MK103: Mounting_Hole; MountingHole_3.7mm
MK104: Mounting_Hole_PAD; MountingHole_3.7mm_Pad

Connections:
GND: MK104.1; also elsewhere on the board

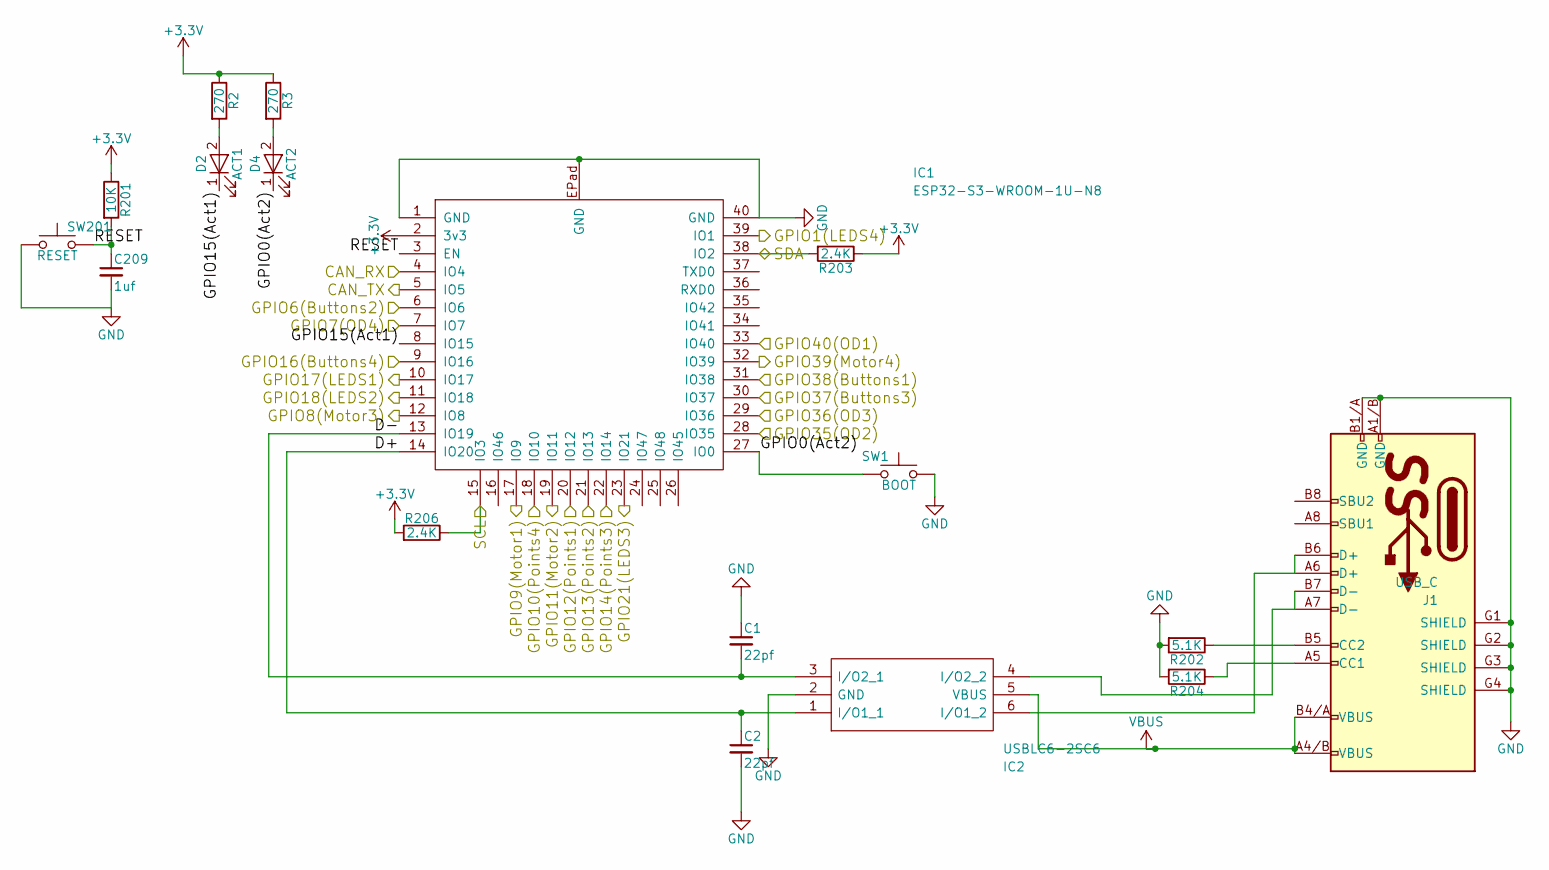
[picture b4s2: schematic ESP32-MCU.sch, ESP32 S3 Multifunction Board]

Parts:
C1, C2: 22pf; C_0402; Mouser Part Number 187-CL05C220JB5NNND
C209: 1uf; C_0402; Mouser Part Number 80-C0402C101K8RAUTO
D2: ACT1; LED_0402; Mouser Part Number 710-150040GS73220
D4: ACT2; LED_0402; Mouser Part Number 710-150040SS73220
IC1: ESP32-S3-WROOM-1U-N8; ESP32_S3_WROOM-1U; Manufacturer_Part_Number ESP32-S3-WROOM-1U-N8; Mouser Part Number 356-ESP32S3WROOM1UN8
IC2: USBLC6-2SC6; SOT-23-6; Mouser Part Number 511-USBLC6-2SC6
J1: USB_C; GCT_USB4105-GF-A; Mouser Part Number 640-USB4105-GF-A-120
R2, R3: 270; R_0402; Mouser Part Number 754-RR0510P-271D
R201: 10K; R_0402; Mouser Part Number 603-RC0402JR-1310KL
R202, R204: 5.1K; R_0402; Mouser Part Number 71-CRCW0402-5.1K-E3
R203, R206: 2.4K; R_0402; Mouser Part Number 71-CRCW06032K40JNEAC
SW1: BOOT; SW_SPST_B3U-1000P-B; Mouser Part Number 653-B3U-1000PM-B
SW201: RESET; SW_SPST_B3U-1000P-B; Mouser Part Number 653-B3U-1000PM-B

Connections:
/Buttons and LEDs/Button1: IC1.31 (IO38); also elsewhere on the board
/Buttons and LEDs/Button2: IC1.6 (IO6); also elsewhere on the board
/Buttons and LEDs/Button3: IC1.30 (IO37); also elsewhere on the board
/Buttons and LEDs/Button4: IC1.9 (IO16); also elsewhere on the board
/CAN Tranceiver/CAN_RX: IC1.4 (IO4); also elsewhere on the board
/CAN Tranceiver/CAN_TX: IC1.5 (IO5); also elsewhere on the board
/ESP32 MCU/D+: C2.1, IC1.14 (IO20), IC2.1 (I/O1_1)
/ESP32 MCU/D-: C1.2, IC1.13 (IO19), IC2.3 (I/O2_1)
/ESP32 MCU/GPIO0(Act2): D4.1 (K), IC1.27 (IO0), SW1.2
/ESP32 MCU/GPIO1(LEDS4): IC1.39 (IO1); also elsewhere on the board
/ESP32 MCU/GPIO7(OD4): IC1.7 (IO7); also elsewhere on the board
/ESP32 MCU/GPIO8(Motor3): IC1.12 (IO8); also elsewhere on the board
/ESP32 MCU/GPIO9(Motor1): IC1.17 (IO9); also elsewhere on the board
/ESP32 MCU/GPIO10(Points4): IC1.18 (IO10); also elsewhere on the board
/ESP32 MCU/GPIO11(Motor2): IC1.19 (IO11); also elsewhere on the board
/ESP32 MCU/GPIO12(Points1): IC1.20 (IO12); also elsewhere on the board
/ESP32 MCU/GPIO13(Points2): IC1.21 (IO13); also elsewhere on the board
/ESP32 MCU/GPIO14(Points3): IC1.22 (IO14); also elsewhere on the board
/ESP32 MCU/GPIO15(Act1): D2.1 (K), IC1.8 (IO15)
/ESP32 MCU/GPIO17(LEDS1): IC1.10 (IO17); also elsewhere on the board
/ESP32 MCU/GPIO18(LEDS2): IC1.11 (IO18); also elsewhere on the board
/ESP32 MCU/GPIO21(LEDS3): IC1.23 (IO21); also elsewhere on the board
/ESP32 MCU/GPIO35(OD2): IC1.28 (IO35); also elsewhere on the board
/ESP32 MCU/GPIO36(OD3): IC1.29 (IO36); also elsewhere on the board
/ESP32 MCU/GPIO39(Motor4): IC1.32 (IO39); also elsewhere on the board
/ESP32 MCU/GPIO40(OD1): IC1.33 (IO40); also elsewhere on the board
/ESP32 MCU/RESET: C209.1, IC1.3 (EN), R201.2, SW201.2
/ESP32 MCU/SCL: IC1.15 (IO3), R206.1; also elsewhere on the board
/ESP32 MCU/SDA: IC1.38 (IO2), R203.2; also elsewhere on the board
GND: C1.1, C2.2, C209.2, IC1.1 (GND), IC1.40 (GND), IC1.EPad (GND), IC2.2 (GND), J1.A1/B (GND), J1.B1/A (GND), J1.G1 (SHIELD), J1.G2 (SHIELD), J1.G3 (SHIELD), J1.G4 (SHIELD), R202.2, R204.2, SW1.1, SW201.1; also elsewhere on the board
unnamed: D2.2 (A), R2.2
unnamed: D4.2 (A), R3.2
unnamed: IC2.4 (I/O2_2), J1.A7 (D-), J1.B7 (D-)
unnamed: IC2.6 (I/O1_2), J1.A6 (D+), J1.B6 (D+)
unnamed: J1.A5 (CC1), R204.1
unnamed: J1.B5 (CC2), R202.1
VBUS: IC2.5 (VBUS), J1.A4/B (VBUS), J1.B4/A (VBUS); also elsewhere on the board

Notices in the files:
ESP32MRNSketches/ESP32-MultiFunction/ESP32-MultiFunction.ino:
Copyright (C) 2019  Robert Heller D/B/A Deepwoods Software
This program is free software; you can redistribute it and/or modify
it under the terms of the GNU General Public License as published by
the Free Software Foundation; either version 2 of the License, or
(at your option) any later version.
ESP32-C3-Booster/ESP32-C3-Booster.kicad_pcb:
(C) Copyright 2022 Robert Heller
LCCCANCape/LCCCANCape.kicad_pcb:
(C) 2023 Robert Heller
PocketBeagleCommandStation/PocketBeagleCommandStation.kicad_pcb:
(C) 2021, 2022 Deepwoods Software
